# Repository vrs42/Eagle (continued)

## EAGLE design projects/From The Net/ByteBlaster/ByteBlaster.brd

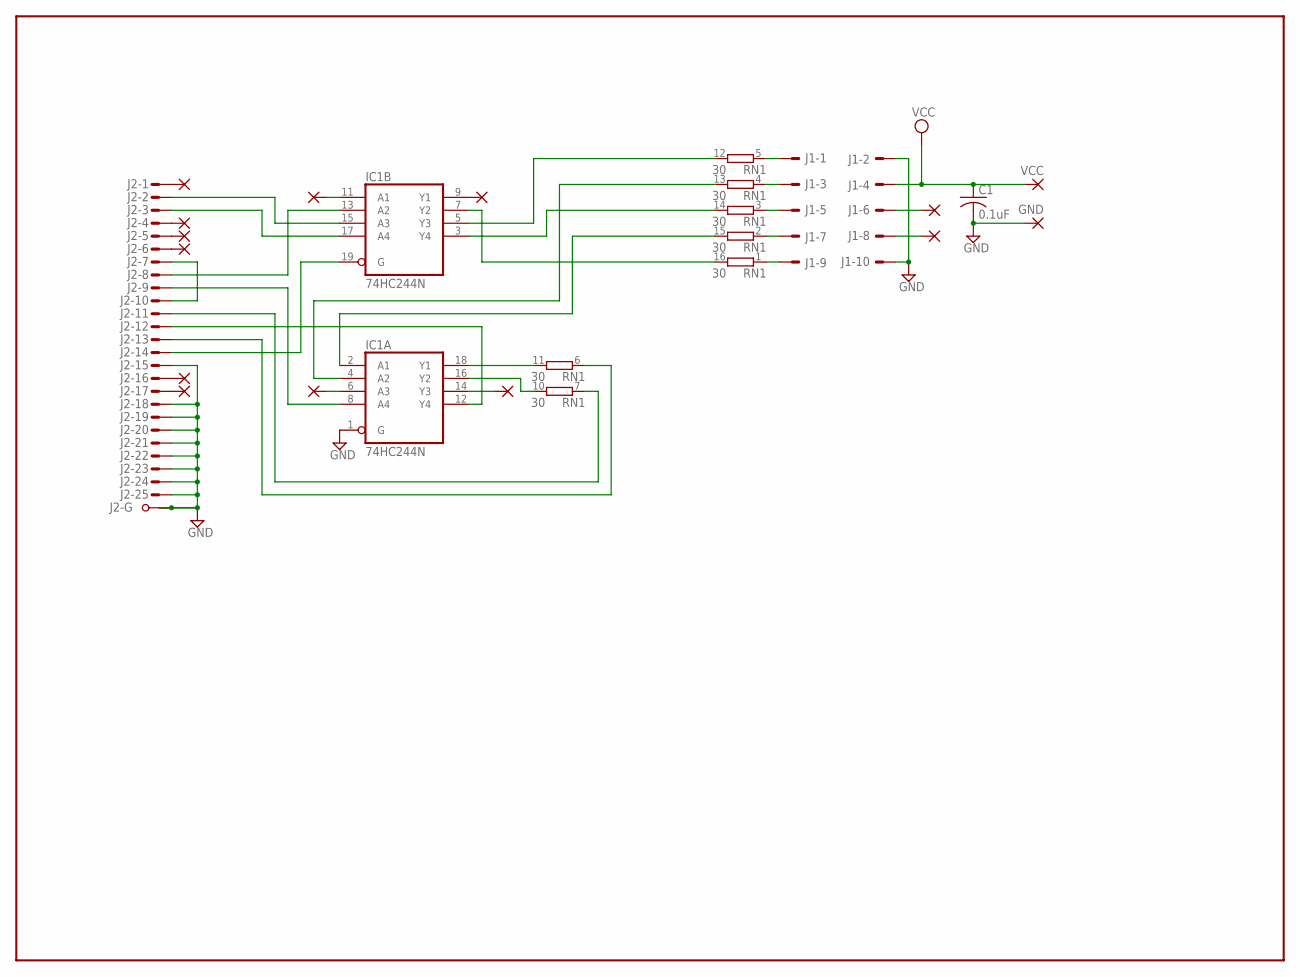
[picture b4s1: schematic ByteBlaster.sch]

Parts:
C1: 0.1uF; C050-025X075
GND: 1,6/0,9
IC1: 74HC244N; DIL20
J1: ML10E; ML10
J2: M25VPS; M25VP
PAD1, PAD2, PAD3, PAD4, PAD5, PAD6, PAD7, PAD8, PAD9, PAD10, PAD11, PAD12: 1,6/0,9
RN1: 30; DIL16
VCC: 1,6/0,9

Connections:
GND: C1.2, GND.1, IC1.1 (G), IC1.10 (GND), J1.2, J1.10, J2.15 (M), J2.18 (M), J2.19 (M), J2.20 (M), J2.21 (M), J2.22 (M), J2.23 (M), J2.24 (M), J2.25 (M), J2.G1, J2.G2
unnamed: J2.1 (M), PAD1.1
unnamed: J2.16 (M), PAD5.1
unnamed: J2.4 (M), PAD2.1
unnamed: J2.5 (M), PAD3.1
unnamed: J2.6 (M), PAD4.1
unnamed: J2.17 (M), PAD6.1
unnamed: IC1.15 (A3), J2.2 (M)
unnamed: IC1.17 (A4), J2.3 (M)
unnamed: J2.7 (M), J2.10 (M)
unnamed: IC1.13 (A2), J2.8 (M)
unnamed: IC1.8 (A4), J2.9 (M)
unnamed: J2.13 (M), RN1.6 (1)
unnamed: IC1.12 (Y4), J2.12 (M)
unnamed: J2.11 (M), RN1.7 (1)
unnamed: IC1.19 (G), J2.14 (M)
unnamed: IC1.11 (A1), PAD7.1
unnamed: IC1.6 (A3), PAD8.1
unnamed: IC1.5 (Y3), RN1.12 (2)
unnamed: IC1.3 (Y4), RN1.14 (2)
unnamed: J1.6, PAD9.1
unnamed: J1.8, PAD10.1
unnamed: J1.9, RN1.1
unnamed: J1.7, RN1.2 (1)
unnamed: J1.5, RN1.3 (1)
unnamed: J1.3, RN1.4 (1)
unnamed: J1.1, RN1.5 (1)
unnamed: IC1.9 (Y1), PAD11.1
unnamed: IC1.14 (Y3), PAD12.1
unnamed: IC1.7 (Y2), RN1.16 (2)
unnamed: IC1.2 (A1), RN1.15 (2)
unnamed: IC1.16 (Y2), RN1.10 (2)
unnamed: IC1.18 (Y1), RN1.11 (2)
unnamed: IC1.4 (A2), RN1.13 (2)
VCC: C1.1, IC1.20 (VCC), J1.4, VCC.1

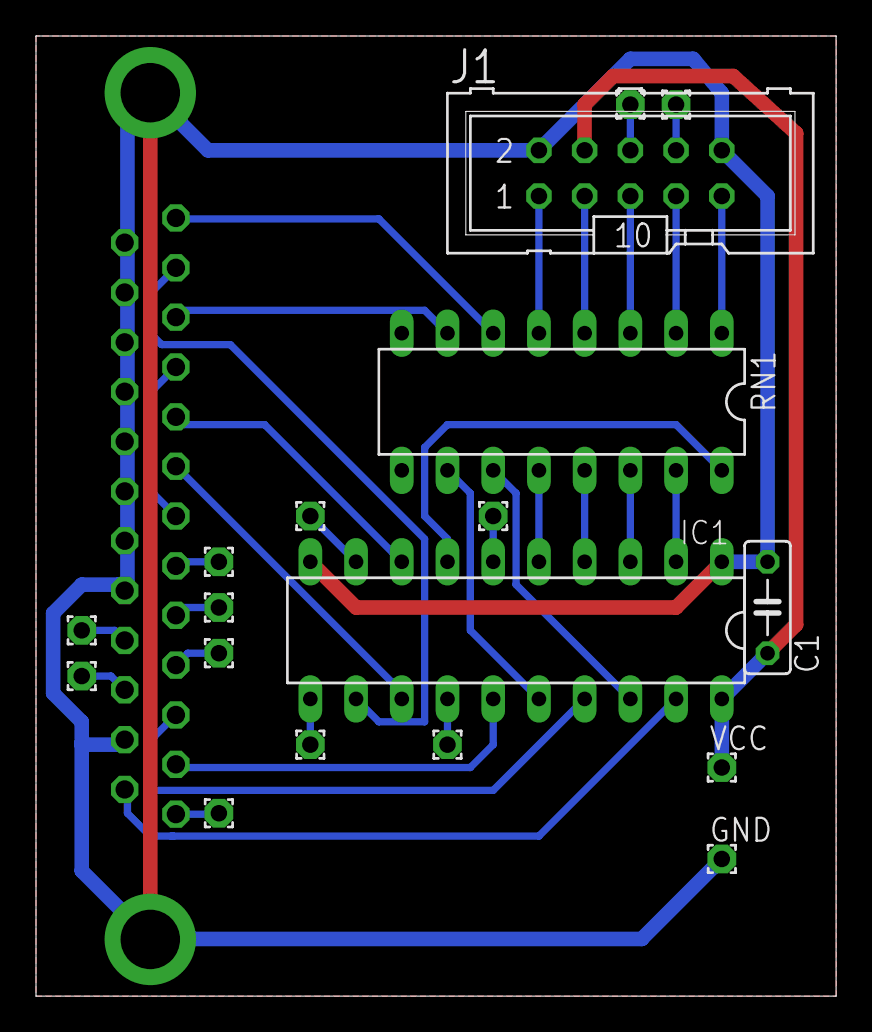
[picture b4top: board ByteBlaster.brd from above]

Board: 2 copper layers, 44.5 x 53.3 mm, 19 parts (1 on the bottom side), 35 nets.

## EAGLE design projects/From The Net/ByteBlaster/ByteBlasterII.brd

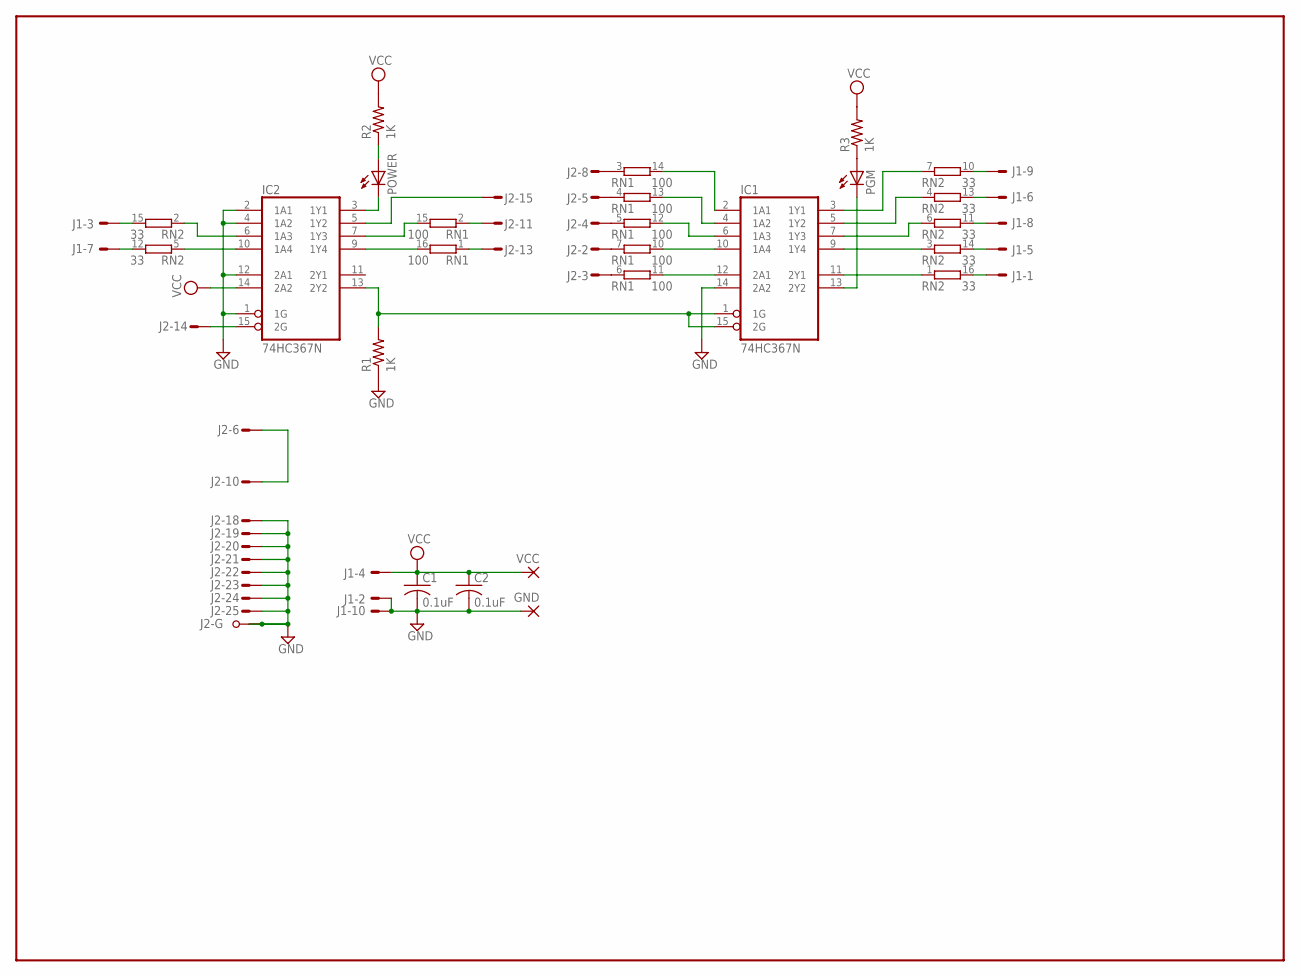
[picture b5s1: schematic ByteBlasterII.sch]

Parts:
C1, C2: 0.1uF; C050-025X075
GND: 1,6/0,9
IC1, IC2: 74HC367N; DIL16
J1: ML10E; ML10
J2: M25VPS; M25VP
PGM: LED3MM
POWER: LED3MM
R1, R2, R3: 1K; 0207/10
RN1: 100; DIL16
RN2: 33; DIL16
VCC: 1,6/0,9

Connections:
GND: C1.2, C2.2, GND.1, IC1.8 (GND), IC1.14 (2A2), IC2.1 (1G), IC2.2 (1A1), IC2.4 (1A2), IC2.8 (GND), IC2.12 (2A1), J1.2, J1.10, J2.18 (M), J2.19 (M), J2.20 (M), J2.21 (M), J2.22 (M), J2.23 (M), J2.24 (M), J2.25 (M), J2.G1, J2.G2, R1.1
unnamed: J1.6, RN2.13 (2)
unnamed: J1.8, RN2.11 (2)
unnamed: J2.8 (M), RN1.3 (1)
unnamed: J2.5 (M), RN1.4 (1)
unnamed: J1.5, RN2.14 (2)
unnamed: J1.9, RN2.10 (2)
unnamed: J2.4 (M), RN1.5 (1)
unnamed: IC1.10 (1A4), RN1.10 (2)
unnamed: J2.6 (M), J2.10 (M)
unnamed: J2.3 (M), RN1.6 (1)
unnamed: IC1.4 (1A2), RN1.13 (2)
unnamed: J2.13 (M), RN1.1
unnamed: J1.1, RN2.16 (2)
unnamed: J2.11 (M), RN1.2 (1)
unnamed: IC1.1 (1G), IC1.15 (2G), IC2.13 (2Y2), R1.2
unnamed: IC2.10 (1A4), RN2.5 (1)
unnamed: IC2.5 (1Y2), J2.15 (M)
unnamed: IC2.6 (1A3), RN2.2 (1)
unnamed: IC1.2 (1A1), RN1.14 (2)
unnamed: IC1.6 (1A3), RN1.12 (2)
unnamed: IC1.12 (2A1), RN1.11 (2)
unnamed: IC2.3 (1Y1), POWER.K (C)
unnamed: J2.2 (M), RN1.7 (1)
unnamed: IC2.9 (1Y4), RN1.16 (2)
unnamed: IC1.11 (2Y1), RN2.1
unnamed: IC2.7 (1Y3), RN1.15 (2)
unnamed: IC2.15 (2G), J2.14 (M)
unnamed: IC1.9 (1Y4), RN2.3 (1)
unnamed: IC1.7 (1Y3), RN2.6 (1)
unnamed: IC1.5 (1Y2), RN2.4 (1)
unnamed: IC1.3 (1Y1), RN2.7 (1)
unnamed: POWER.A, R2.1
unnamed: IC1.13 (2Y2), PGM.K (C)
unnamed: PGM.A, R3.1
unnamed: J1.3, RN2.15 (2)
unnamed: J1.7, RN2.12 (2)
VCC: C1.1, C2.1, IC1.16 (VCC), IC2.14 (2A2), IC2.16 (VCC), J1.4, R2.2, R3.2, VCC.1

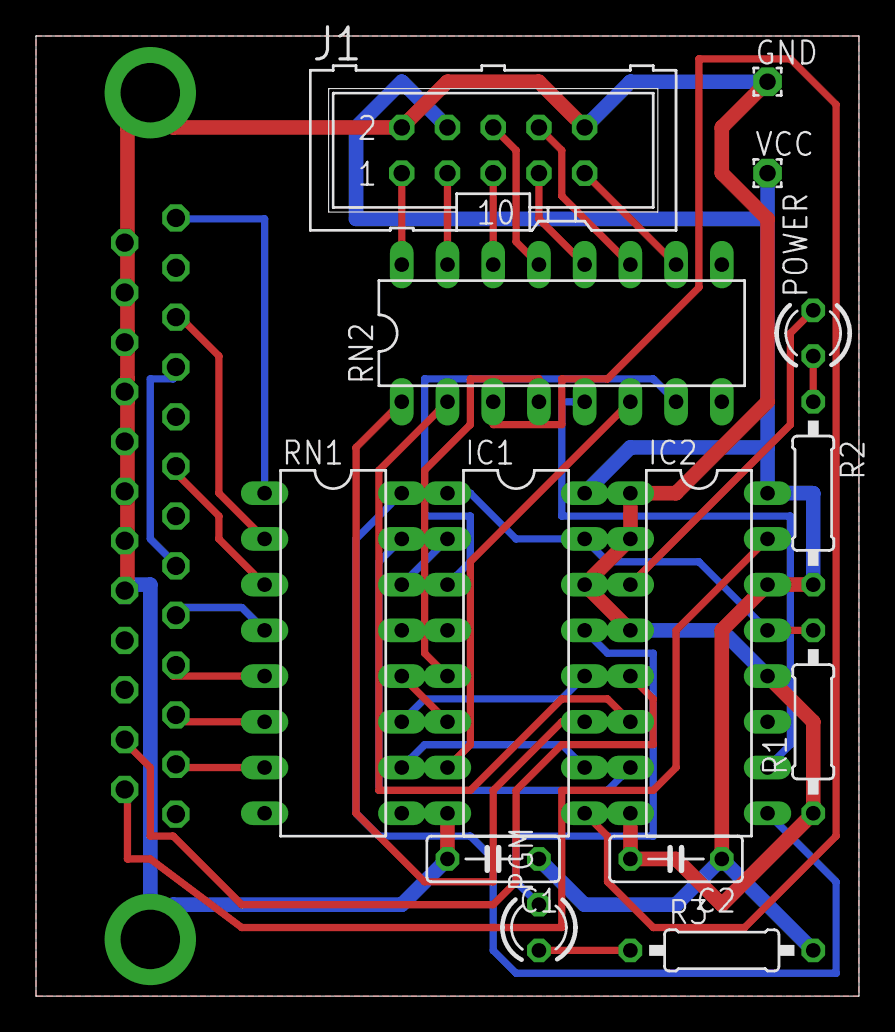
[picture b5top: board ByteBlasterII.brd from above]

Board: 2 copper layers, 45.7 x 53.3 mm, 15 parts (1 on the bottom side), 38 nets.

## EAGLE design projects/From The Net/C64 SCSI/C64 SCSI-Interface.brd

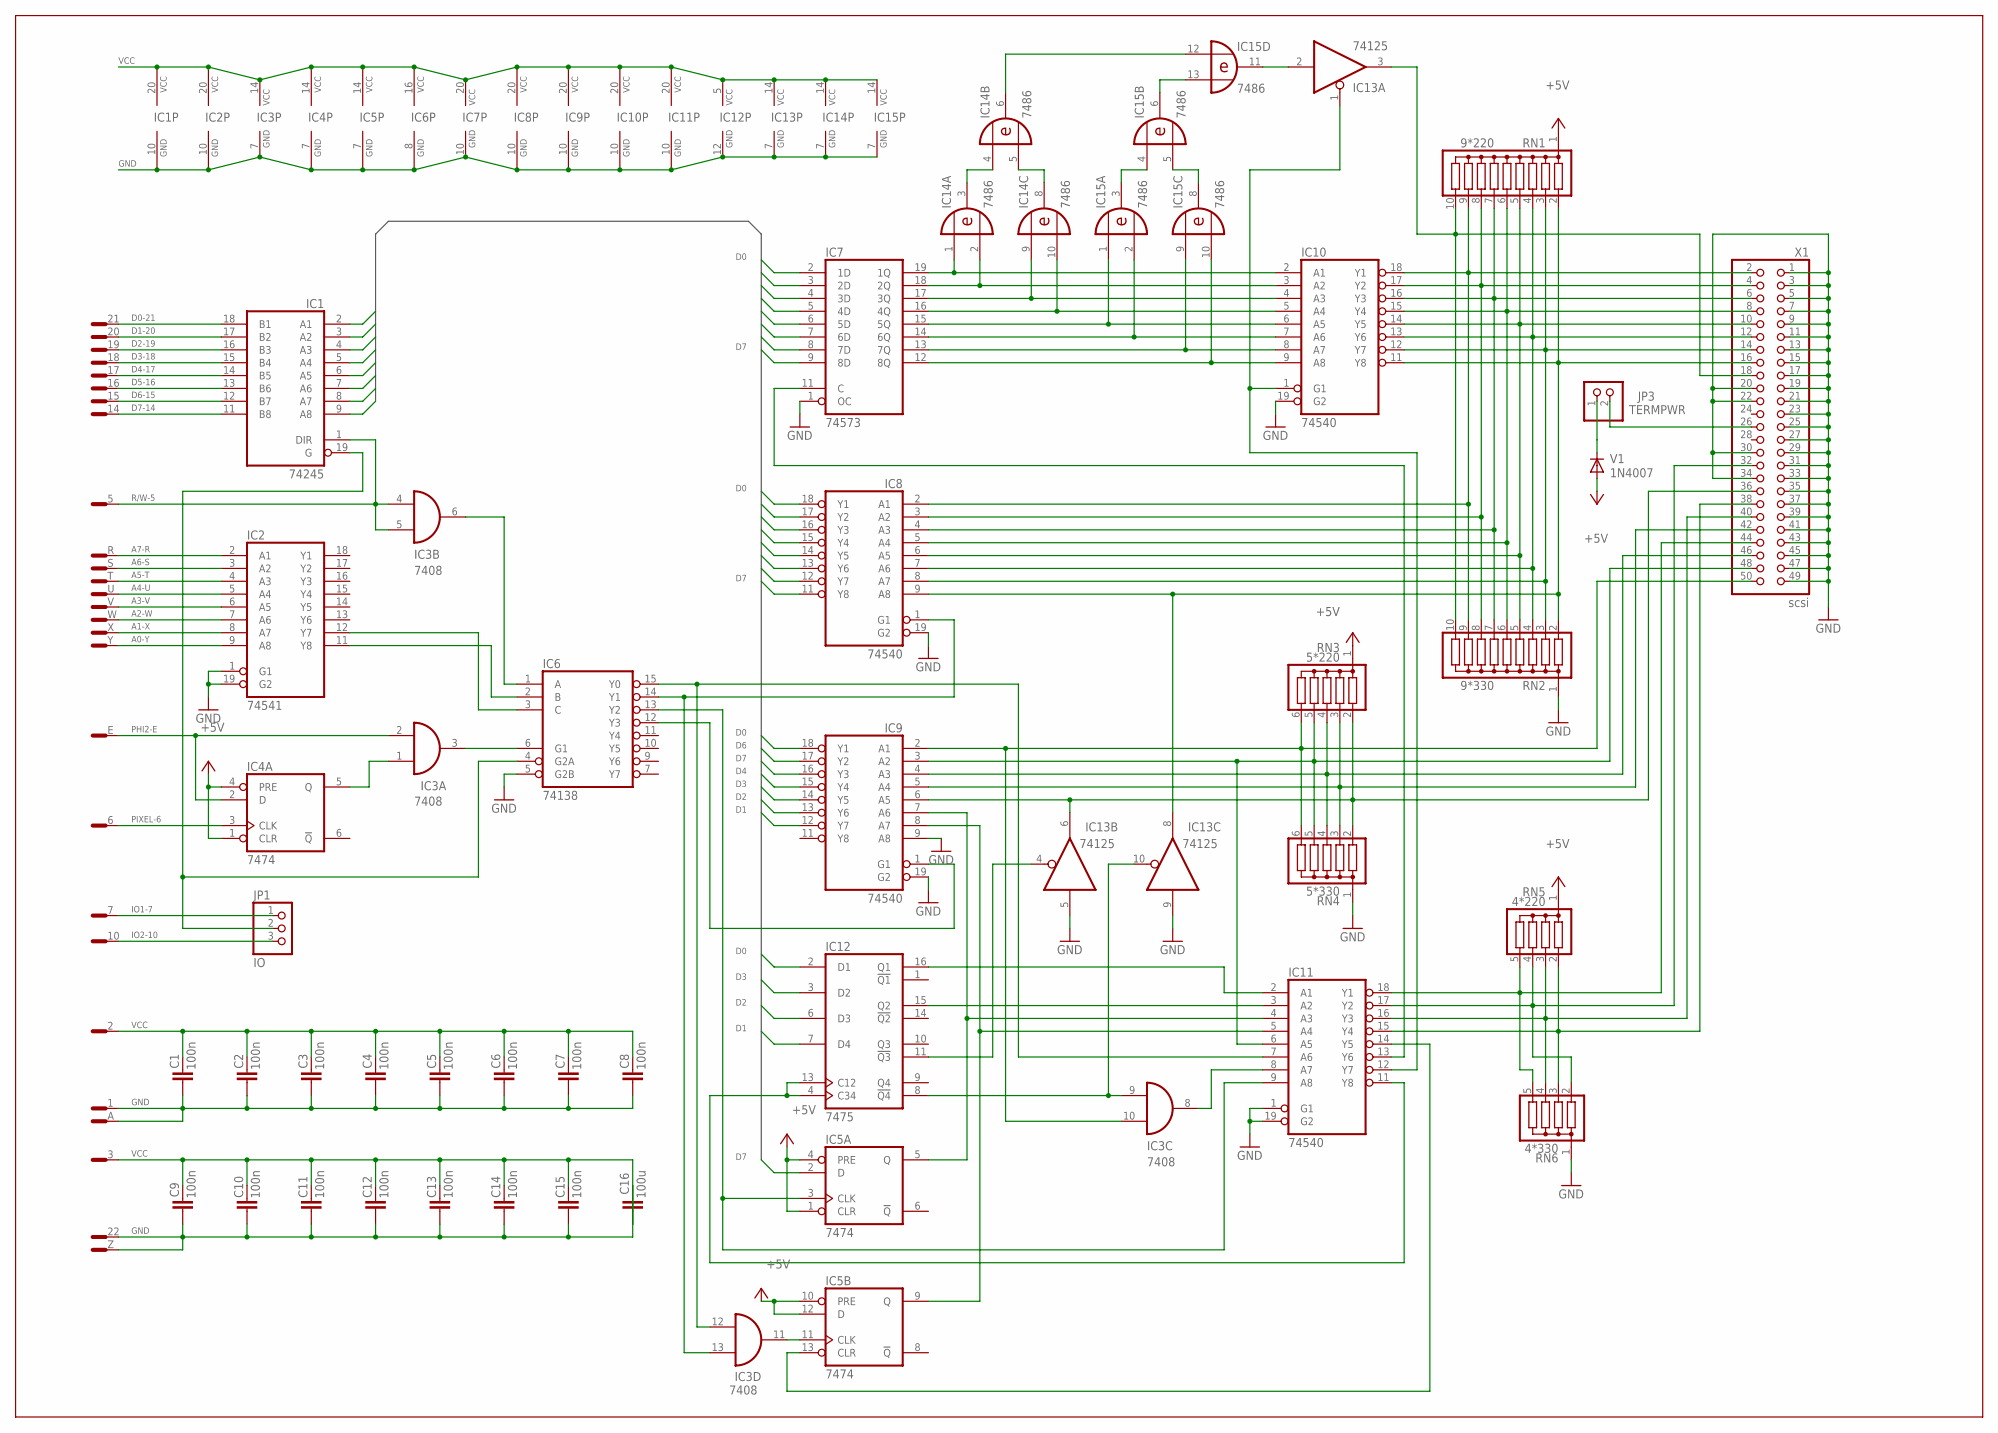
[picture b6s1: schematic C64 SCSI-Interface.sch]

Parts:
C1, C2, C3, C4, C5, C6, C7, C8, C9, C10, C11, C12, C13, C14, C15: 100n; C050-025X075
C16: 100u; C050-025X075
IC1: 74245; DIL20
IC2: 74541; DIL20
IC3: 7408; DIL14
IC4, IC5: 7474; DIL14
IC6: 74138; DIL16
IC7: 74573; DIL20
IC8, IC9, IC10, IC11: 74540; DIL20
IC12: 7475; DIL16
IC13: 74125; DIL14
IC14, IC15: 7486; DIL14
JP1: IO; 1X03
JP3: TERMPWR; 1X02
RN1: 9*220; SIL10
RN2: 9*330; SIL10
RN3: 5*220; SIL6
RN4: 5*330; SIL6
RN5: 4*220; SIL5
RN6: 4*330; SIL5
V1: 1N4007; DO41-10
X1: scsi; 2X25
X2: CARDCON22; CARDCON2

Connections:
A0: IC2.11 (Y8), IC6.2 (B)
A0-Y: IC2.9 (A8), X2.Y
A1: IC2.12 (Y7), IC6.3 (C)
A1-X: IC2.8 (A7), X2.X
A2-W: IC2.7 (A6), X2.W
A3-V: IC2.6 (A5), X2.V
A4-U: IC2.5 (A4), X2.U
A5-T: IC2.4 (A3), X2.T
A6-S: IC2.3 (A2), X2.S
A7-R: IC2.2 (A1), X2.R
D0: IC1.2 (A1), IC7.2 (1D), IC8.18 (Y1), IC9.18 (Y1), IC12.2 (D1)
D0-21: IC1.18 (B1), X2.21
D1: IC1.3 (A2), IC7.3 (2D), IC8.17 (Y2), IC9.12 (Y7), IC12.7 (D4)
D1-20: IC1.17 (B2), X2.20
D2: IC1.4 (A3), IC7.4 (3D), IC8.16 (Y3), IC9.13 (Y6), IC12.6 (D3)
D2-19: IC1.16 (B3), X2.19
D3: IC1.5 (A4), IC7.5 (4D), IC8.15 (Y4), IC9.14 (Y5), IC12.3 (D2)
D3-18: IC1.15 (B4), X2.18
D4: IC1.6 (A5), IC7.6 (5D), IC8.14 (Y5), IC9.15 (Y4)
D4-17: IC1.14 (B5), X2.17
D5: IC1.7 (A6), IC7.7 (6D), IC8.13 (Y6)
D5-16: IC1.13 (B6), X2.16
D6: IC1.8 (A7), IC7.8 (7D), IC8.12 (Y7), IC9.17 (Y2)
D6-15: IC1.12 (B7), X2.15
D7: IC1.9 (A8), IC5.2 (D), IC7.9 (8D), IC8.11 (Y8), IC9.16 (Y3)
D7-14: IC1.11 (B8), X2.14
GND: C1.1, C2.1, C3.1, C4.1, C5.1, C6.1, C7.1, C8.1, C9.1, C10.1, C11.1, C12.1, C13.1, C14.1, C15.1, C16.2, IC1.10 (GND), IC2.1 (G1), IC2.10 (GND), IC2.19 (G2), IC3.7 (GND), IC4.7 (GND), IC5.7 (GND), IC6.5 (G2B), IC6.8 (GND), IC7.1 (OC), IC7.10 (GND), IC8.10 (GND), IC8.19 (G2), IC9.9 (A8), IC9.10 (GND), IC9.19 (G2), IC10.10 (GND), IC10.19 (G2), IC11.1 (G1), IC11.10 (GND), IC11.19 (G2), IC12.12 (GND), IC13.5 (I), IC13.7 (GND), IC13.9 (I), IC14.7 (GND), IC15.7 (GND), RN2.1, RN4.1, RN6.1, X1.1, X1.3, X1.5, X1.7, X1.9, X1.11, X1.13, X1.15, X1.17, X1.19, X1.20, X1.21, X1.22, X1.23, X1.25, X1.27, X1.29, X1.30, X1.31, X1.33, X1.34, X1.35, X1.37, X1.39, X1.41, X1.43, X1.45, X1.47, X1.49, X2.1, X2.22, X2.A, X2.Z
IO: IC1.19 (G), IC6.4 (G2A), JP1.2
IO1-7: JP1.1, X2.7
IO2-10: JP1.3, X2.10
unnamed: IC14.3 (O), IC14.4 (I0)
unnamed: IC3.1 (I0), IC4.5 (Q)
unnamed: IC6.12 (Y3), IC9.1 (G1)
unnamed: IC14.5 (I1), IC14.8 (O)
unnamed: IC14.6 (O), IC15.12 (I0)
unnamed: IC15.6 (O), IC15.13 (I1)
unnamed: IC15.3 (O), IC15.4 (I0)
unnamed: IC15.5 (I1), IC15.8 (O)
unnamed: IC3.11 (O), IC5.11 (CLK)
unnamed: IC7.19 (1Q), IC10.2 (A1), IC14.1 (I0)
unnamed: IC7.18 (2Q), IC10.3 (A2), IC14.2 (I1)
unnamed: IC7.17 (3Q), IC10.4 (A3), IC14.9 (I0)
unnamed: IC7.16 (4Q), IC10.5 (A4), IC14.10 (I1)
unnamed: IC7.15 (5Q), IC10.6 (A5), IC15.1 (I0)
unnamed: IC7.14 (6Q), IC10.7 (A6), IC15.2 (I1)
unnamed: IC7.13 (7Q), IC10.8 (A7), IC15.9 (I0)
unnamed: IC7.12 (8Q), IC10.9 (A8), IC15.10 (I1)
unnamed: IC13.2 (I), IC15.11 (O)
unnamed: IC10.1 (G1), IC11.12 (Y7), IC13.1 (OE)
unnamed: IC8.9 (A8), IC10.11 (Y8), IC13.8 (O), RN1.2, RN2.2, X1.16
unnamed: IC8.8 (A7), IC10.12 (Y7), RN1.3, RN2.3, X1.14
unnamed: IC8.7 (A6), IC10.13 (Y6), RN1.4, RN2.4, X1.12
unnamed: IC8.6 (A5), IC10.14 (Y5), RN1.5, RN2.5, X1.10
unnamed: IC8.5 (A4), IC10.15 (Y4), RN1.6, RN2.6, X1.8
unnamed: IC8.4 (A3), IC10.16 (Y3), RN1.7, RN2.7, X1.6
unnamed: IC8.3 (A2), IC10.17 (Y2), RN1.8, RN2.8, X1.4
unnamed: IC8.2 (A1), IC10.18 (Y1), RN1.9, RN2.9, X1.2
unnamed: IC13.3 (O), RN1.10, RN2.10, X1.18
unnamed: IC3.9 (I0), IC12.8 (!Q4), IC13.10 (OE)
unnamed: IC12.11 (!Q3), IC13.4 (OE)
unnamed: IC9.6 (A5), IC13.6 (O), RN3.2, RN4.2, X1.36
unnamed: IC9.5 (A4), RN3.3, RN4.3, X1.42
unnamed: IC9.4 (A3), RN3.4, RN4.4, X1.46
unnamed: IC9.3 (A2), IC11.6 (A5), RN3.5, RN4.5, X1.48
unnamed: IC3.10 (I1), IC9.2 (A1), RN3.6, RN4.6, X1.50
unnamed: IC5.9 (Q), IC9.8 (A7), IC11.5 (A4)
unnamed: IC11.15 (Y4), RN5.2, RN6.3, X1.38
unnamed: IC11.16 (Y3), RN5.3, RN6.4, X1.40
unnamed: IC11.17 (Y2), RN5.4, RN6.2, X1.32
unnamed: IC11.18 (Y1), RN5.5, RN6.5, X1.44
unnamed: IC3.12 (I0), IC6.15 (Y0), IC11.7 (A6)
unnamed: IC5.3 (CLK), IC6.13 (Y2), IC11.9 (A8)
unnamed: IC5.5 (Q), IC9.7 (A6), IC11.4 (A3)
unnamed: IC3.13 (I1), IC6.14 (Y1), IC8.1 (G1)
unnamed: IC11.11 (Y8), IC12.4 (C34), IC12.13 (C12)
unnamed: IC11.2 (A1), IC12.16 (Q1)
unnamed: IC11.3 (A2), IC12.15 (Q2)
unnamed: IC5.13 (CLR), IC11.14 (Y5)
unnamed: IC3.8 (O), IC11.8 (A7)
unnamed: IC7.11 (C), IC11.13 (Y6)
unnamed: JP3.1, V1.C
PHI2: IC3.3 (O), IC6.6 (G1)
PHI2-E: IC3.2 (I1), IC4.2 (D), X2.E
PIXEL-6: IC4.3 (CLK), X2.6
R/-W: IC3.6 (O), IC6.1 (A)
R/W-5: IC1.1 (DIR), IC3.4 (I0), IC3.5 (I1), X2.5
TERMPWR: JP3.2, X1.26
VCC: C1.2, C2.2, C3.2, C4.2, C5.2, C6.2, C7.2, C8.2, C9.2, C10.2, C11.2, C12.2, C13.2, C14.2, C15.2, C16.1, IC1.20 (VCC), IC2.20 (VCC), IC3.14 (VCC), IC4.1 (CLR), IC4.4 (PRE), IC4.14 (VCC), IC5.1 (CLR), IC5.4 (PRE), IC5.10 (PRE), IC5.12 (D), IC5.14 (VCC), IC6.16 (VCC), IC7.20 (VCC), IC8.20 (VCC), IC9.20 (VCC), IC10.20 (VCC), IC11.20 (VCC), IC12.5 (VCC), IC13.14 (VCC), IC14.14 (VCC), IC15.14 (VCC), RN1.1, RN3.1, RN5.1, V1.A, X2.2, X2.3

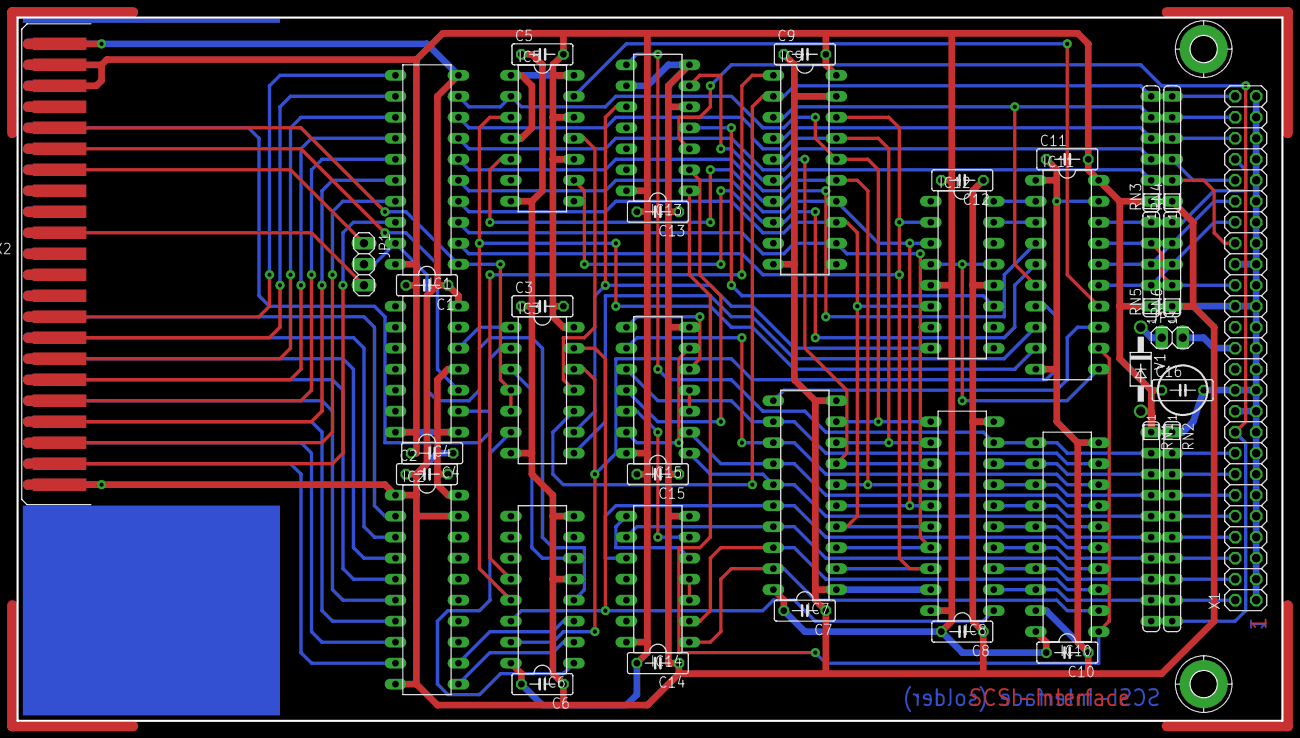
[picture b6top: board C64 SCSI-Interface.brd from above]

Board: 2 copper layers, 153.0 x 85.1 mm, 44 parts (0 on the bottom side), 88 nets.

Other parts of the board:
E$1, E$2: BO3,2-P

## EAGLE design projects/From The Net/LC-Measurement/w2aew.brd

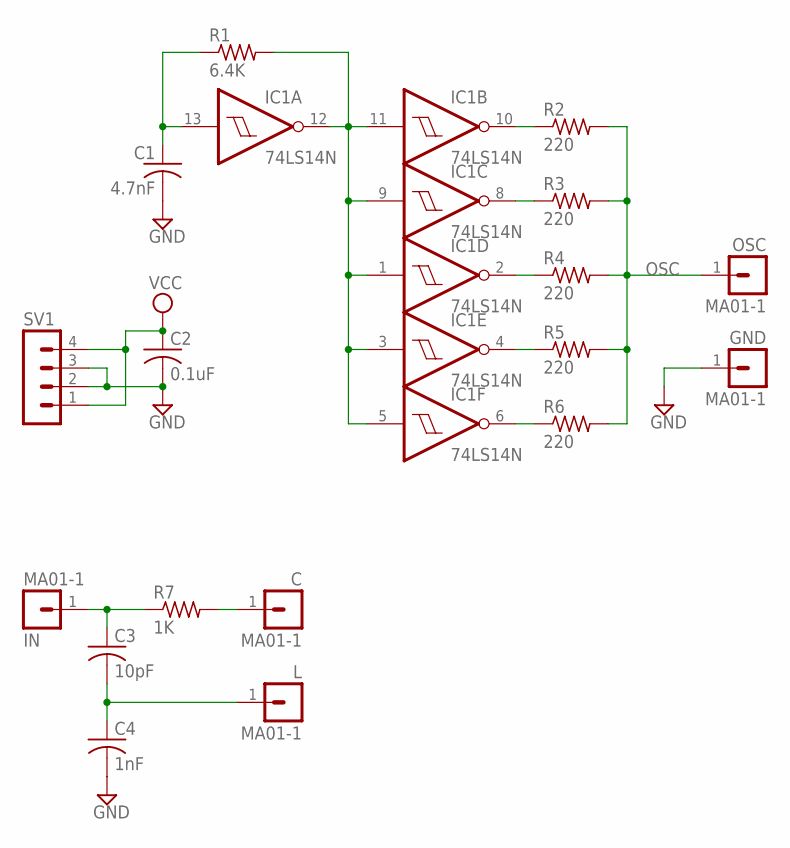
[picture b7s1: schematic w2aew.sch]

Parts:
C: MA01-1
C1: 4.7nF; C050-025X075
C2: 0.1uF; C050-025X075
C3: 10pF; C050-025X075
C4: 1nF; C050-025X075
GND: MA01-1
IC1: 74LS14N; DIL14
IN: MA01-1
L: MA01-1
OSC: MA01-1
R1: 6.4K; 0207/10
R2, R3, R4, R5, R6: 220; 0207/10
R7: 1K; 0207/10
SV1: MA04-1

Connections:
GND: C1.2, C2.2, C4.2, GND.1, IC1.7 (GND), SV1.2, SV1.3
unnamed: C1.1, IC1.13 (I), R1.1
unnamed: IC1.1 (I), IC1.3 (I), IC1.5 (I), IC1.9 (I), IC1.11 (I), IC1.12 (O), R1.2
unnamed: IC1.10 (O), R2.1
unnamed: IC1.8 (O), R3.1
unnamed: IC1.2 (O), R4.1
unnamed: IC1.4 (O), R5.1
unnamed: IC1.6 (O), R6.1
unnamed: C3.1, IN.1, R7.1
unnamed: C.1, R7.2
unnamed: C3.2, C4.1, L.1
OSC: OSC.1, R2.2, R3.2, R4.2, R5.2, R6.2
VCC: C2.1, IC1.14 (VCC), SV1.1, SV1.4

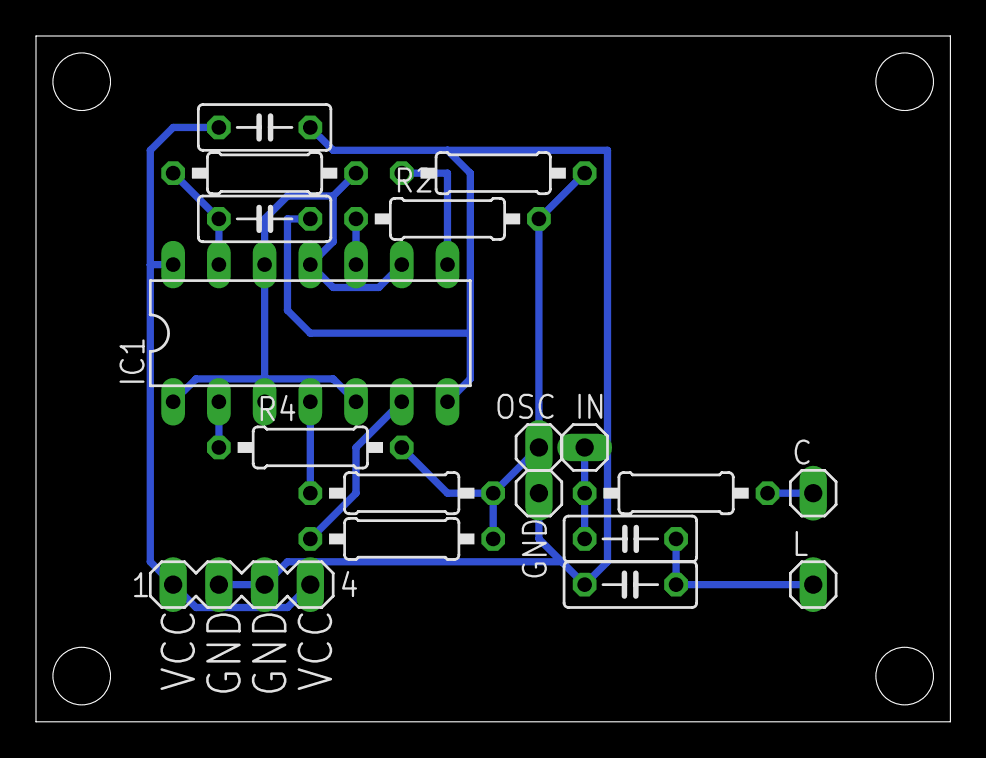
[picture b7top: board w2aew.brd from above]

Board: 2 copper layers, 50.8 x 38.1 mm, 18 parts (0 on the bottom side), 13 nets.
